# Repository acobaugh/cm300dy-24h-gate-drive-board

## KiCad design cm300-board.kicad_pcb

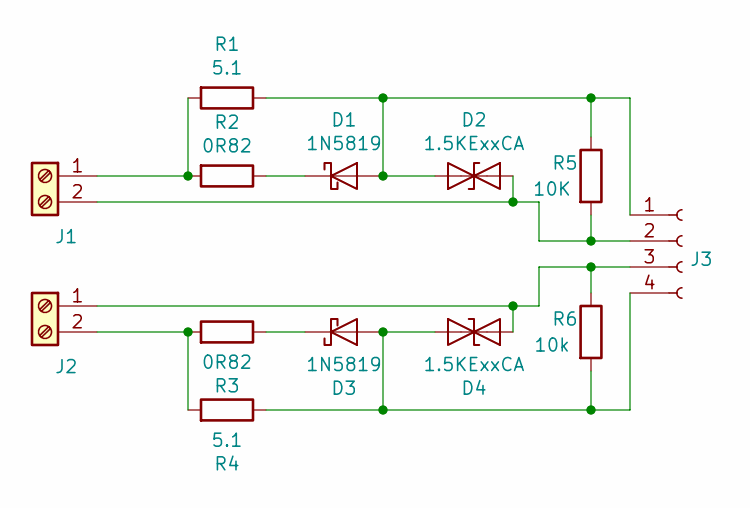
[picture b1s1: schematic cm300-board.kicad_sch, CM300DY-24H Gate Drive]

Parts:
D1, D3: 1N5819; D_SOD-123; MPN 1N5819HW-7-F
D2, D4: 1.5KExxCA; D_SMC; MPN SMCJ1.5KE24CA-TP
J1, J2: Screw_Terminal_01x02; Molex_KK-254_AE-6410-02A_1x02_P2.54mm_Vertical; MPN 0022272021
J3: Conn_01x04_Female; IGBT-CM300DY-GATE; MPN 3534; digikey 36-3534-ND
R1, R4: 5.1; R_2512_6332Metric_Pad1.40x3.35mm_HandSolder; MPN CRM2512-FX-5R10ELF
R2, R3: 0R82; R_2512_6332Metric_Pad1.40x3.35mm_HandSolder; MPN CRM2512-FX-R820ELF
R5: 10K; R_1206_3216Metric_Pad1.30x1.75mm_HandSolder; MPN RMCF1206FT10K0
R6: 10k; R_1206_3216Metric_Pad1.30x1.75mm_HandSolder; MPN RMCF1206FT10K0

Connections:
unnamed: D1.2 (A), D2.1 (A1), J3.1, R1.1, R5.1
unnamed: D1.1 (K), R2.1
unnamed: D2.2 (A2), J1.2, J3.2, R5.2
unnamed: D3.2 (A), D4.1 (A1), J3.4, R4.1, R6.2
unnamed: D3.1 (K), R3.1
unnamed: D4.2 (A2), J2.1, J3.3, R6.1
unnamed: J1.1, R1.2, R2.2
unnamed: J2.2, R3.2, R4.2

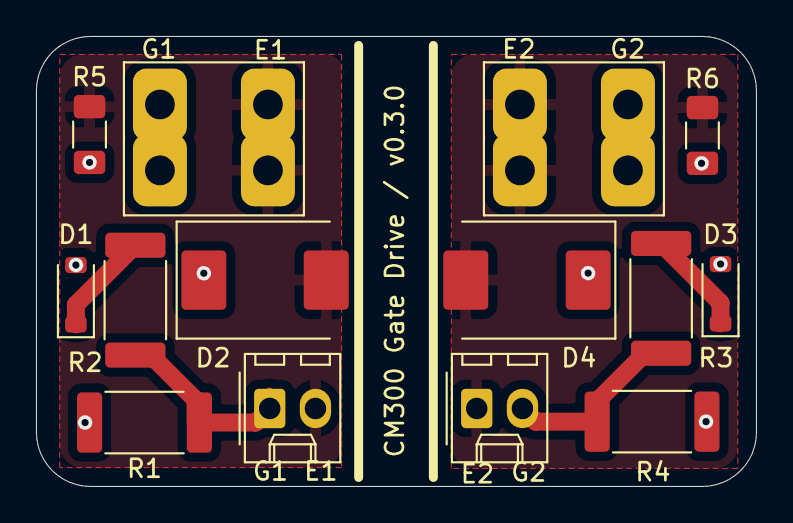
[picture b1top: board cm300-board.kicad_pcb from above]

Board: 2 copper layers, 40.0 x 25.0 mm, 13 parts (0 on the bottom side), 8 nets.

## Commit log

2020-01-19 add board layout pdf
2023-05-14 switch to smd
2023-05-14 regenerate drill and gerber files
2023-05-14 regenerate drill file
2024-01-13 feat: convert to SMD, add Rge
2024-08-20 add gitignore
